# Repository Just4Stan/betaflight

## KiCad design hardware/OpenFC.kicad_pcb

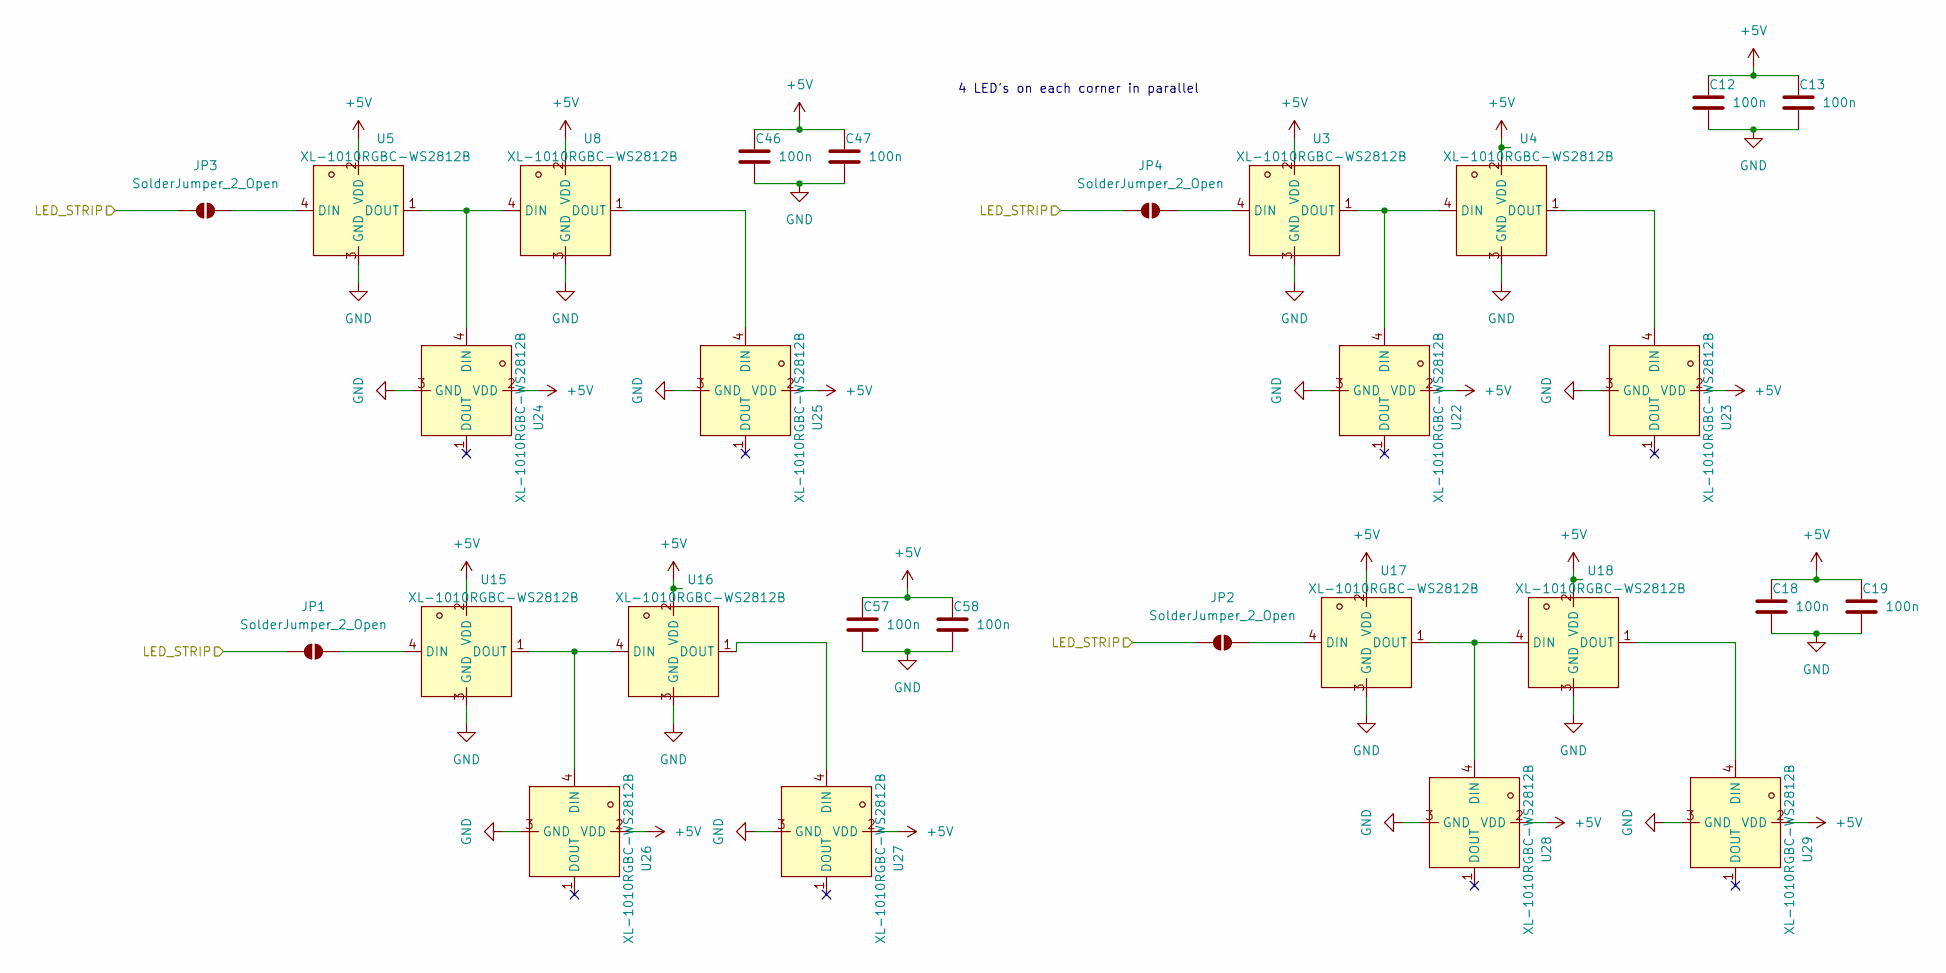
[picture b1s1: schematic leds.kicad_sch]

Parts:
C12, C13, C18, C19, C46, C47, C57, C58: 100n; C_0402_1005Metric; LCSC C1525
JP1, JP2, JP3, JP4: SolderJumper_2_Open; MouseBite-Slot-Jumper_0201
U3, U4, U5, U8, U15, U16, U17, U18, U22, U23, U24, U25, U26, U27, U28, U29: XL-1010RGBC-WS2812B; LED-SMD_4P-L1.0-W1.0-TL_XL-1010RGBC-WS2812B; LCSC Part C5349953

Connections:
+5V: C12.1, C13.1, C18.1, C19.1, C46.1, C47.1, C57.1, C58.1, U3.2 (VDD), U4.2 (VDD), U5.2 (VDD), U8.2 (VDD), U15.2 (VDD), U16.2 (VDD), U17.2 (VDD), U18.2 (VDD), U22.2 (VDD), U23.2 (VDD), U24.2 (VDD), U25.2 (VDD), U26.2 (VDD), U27.2 (VDD), U28.2 (VDD), U29.2 (VDD); also elsewhere on the board
/LED: JP1.1 (A), JP2.1 (A), JP3.1 (A), JP4.1 (A); also elsewhere on the board
GND: C12.2, C13.2, C18.2, C19.2, C46.2, C47.2, C57.2, C58.2, U3.3 (GND), U4.3 (GND), U5.3 (GND), U8.3 (GND), U15.3 (GND), U16.3 (GND), U17.3 (GND), U18.3 (GND), U22.3 (GND), U23.3 (GND), U24.3 (GND), U25.3 (GND), U26.3 (GND), U27.3 (GND), U28.3 (GND), U29.3 (GND); also elsewhere on the board
unnamed: JP1.2 (B), U15.4 (DIN)
unnamed: JP2.2 (B), U17.4 (DIN)
unnamed: JP3.2 (B), U5.4 (DIN)
unnamed: JP4.2 (B), U3.4 (DIN)
unnamed: U15.1 (DOUT), U16.4 (DIN), U26.4 (DIN)
unnamed: U16.1 (DOUT), U27.4 (DIN)
unnamed: U17.1 (DOUT), U18.4 (DIN), U28.4 (DIN)
unnamed: U18.1 (DOUT), U29.4 (DIN)
unnamed: U3.1 (DOUT), U4.4 (DIN), U22.4 (DIN)
unnamed: U4.1 (DOUT), U23.4 (DIN)
unnamed: U5.1 (DOUT), U8.4 (DIN), U24.4 (DIN)
unnamed: U8.1 (DOUT), U25.4 (DIN)

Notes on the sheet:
4 LED's on each corner in parallel

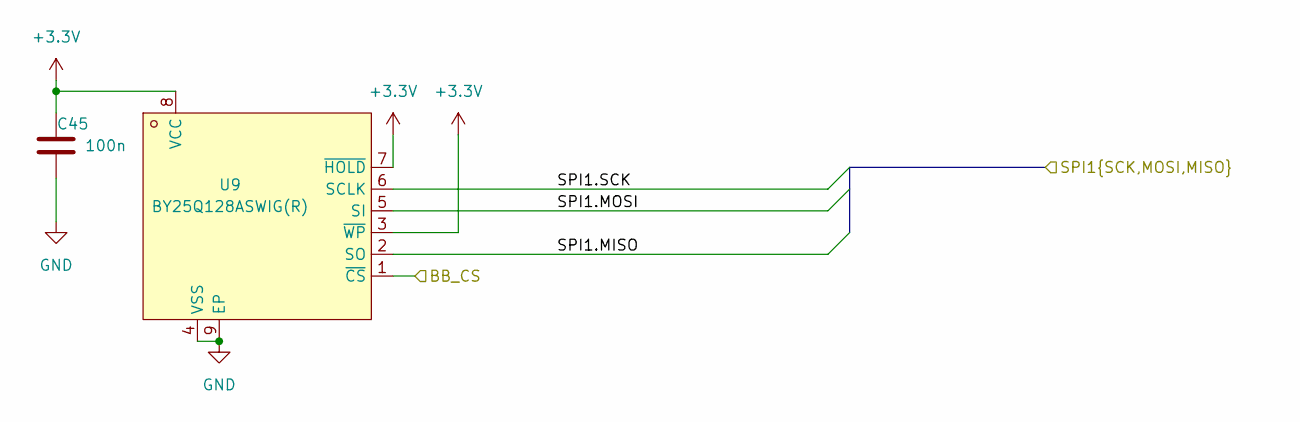
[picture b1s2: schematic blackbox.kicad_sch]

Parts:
C45: 100n; C_0402_1005Metric; LCSC C1525
U9: BY25Q128ASWIG(R); WSON-8_L6.0-W5.0-P1.27-BL-EP; LCSC Part C394872

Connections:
+3.3V: C45.1, U9.3 (~WP), U9.7 (~HOLD), U9.8 (VCC); also elsewhere on the board
/BLACKBOX/BB_CS: U9.1 (~CS); also elsewhere on the board
/BLACKBOX/SPI1.MISO: U9.2 (SO); also elsewhere on the board
/BLACKBOX/SPI1.MOSI: U9.5 (SI); also elsewhere on the board
/BLACKBOX/SPI1.SCK: U9.6 (SCLK); also elsewhere on the board
GND: C45.2, U9.4 (VSS), U9.9 (EP); also elsewhere on the board

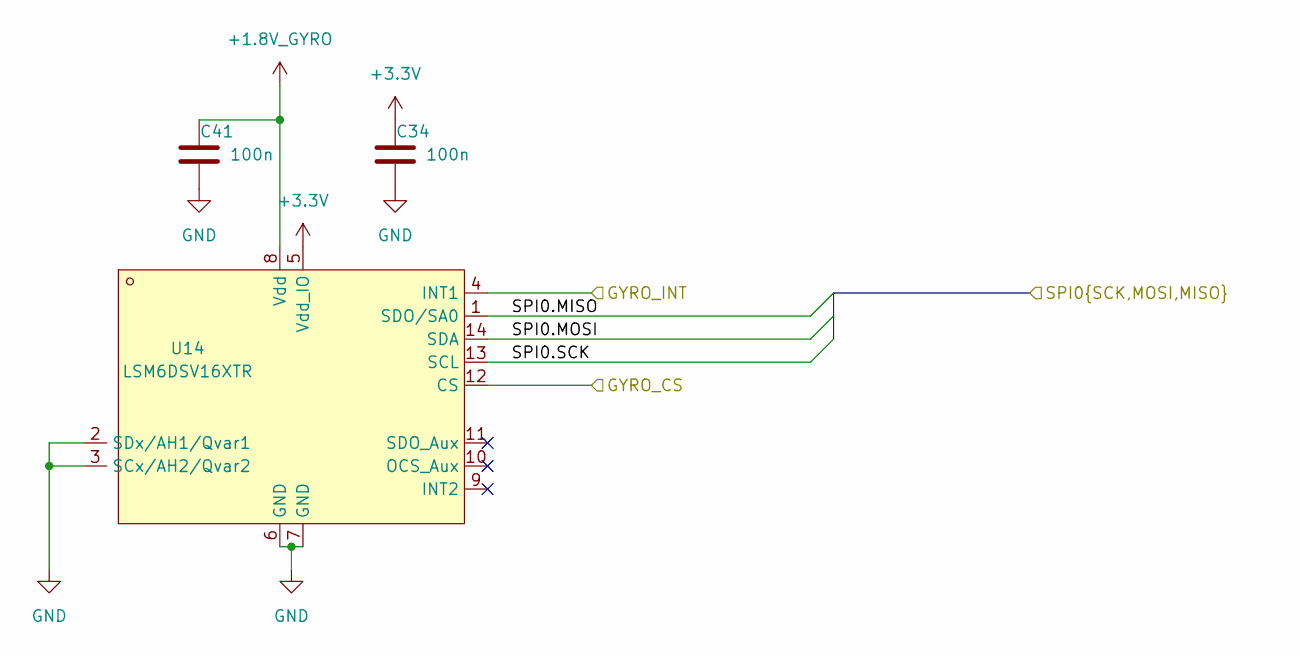
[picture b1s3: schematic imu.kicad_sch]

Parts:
C34, C41: 100n; C_0402_1005Metric; LCSC C1525
U14: LSM6DSV16XTR; LGA-14_L3.0-W2.5-P0.50-BR; LCSC Part C5267406

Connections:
+1.8V_GYRO: C41.1, U14.8 (Vdd); also elsewhere on the board
+3.3V: C34.1, U14.5 (Vdd_IO); also elsewhere on the board
/IMU/GYRO_CS: U14.12 (CS); also elsewhere on the board
/IMU/GYRO_INT: U14.4 (INT1); also elsewhere on the board
/IMU/SPI0.MISO: U14.1 (SDO/SA0); also elsewhere on the board
/IMU/SPI0.MOSI: U14.14 (SDA); also elsewhere on the board
/IMU/SPI0.SCK: U14.13 (SCL); also elsewhere on the board
GND: C34.2, C41.2, U14.2 (SDx/AH1/Qvar1), U14.3 (SCx/AH2/Qvar2), U14.6 (GND), U14.7 (GND); also elsewhere on the board

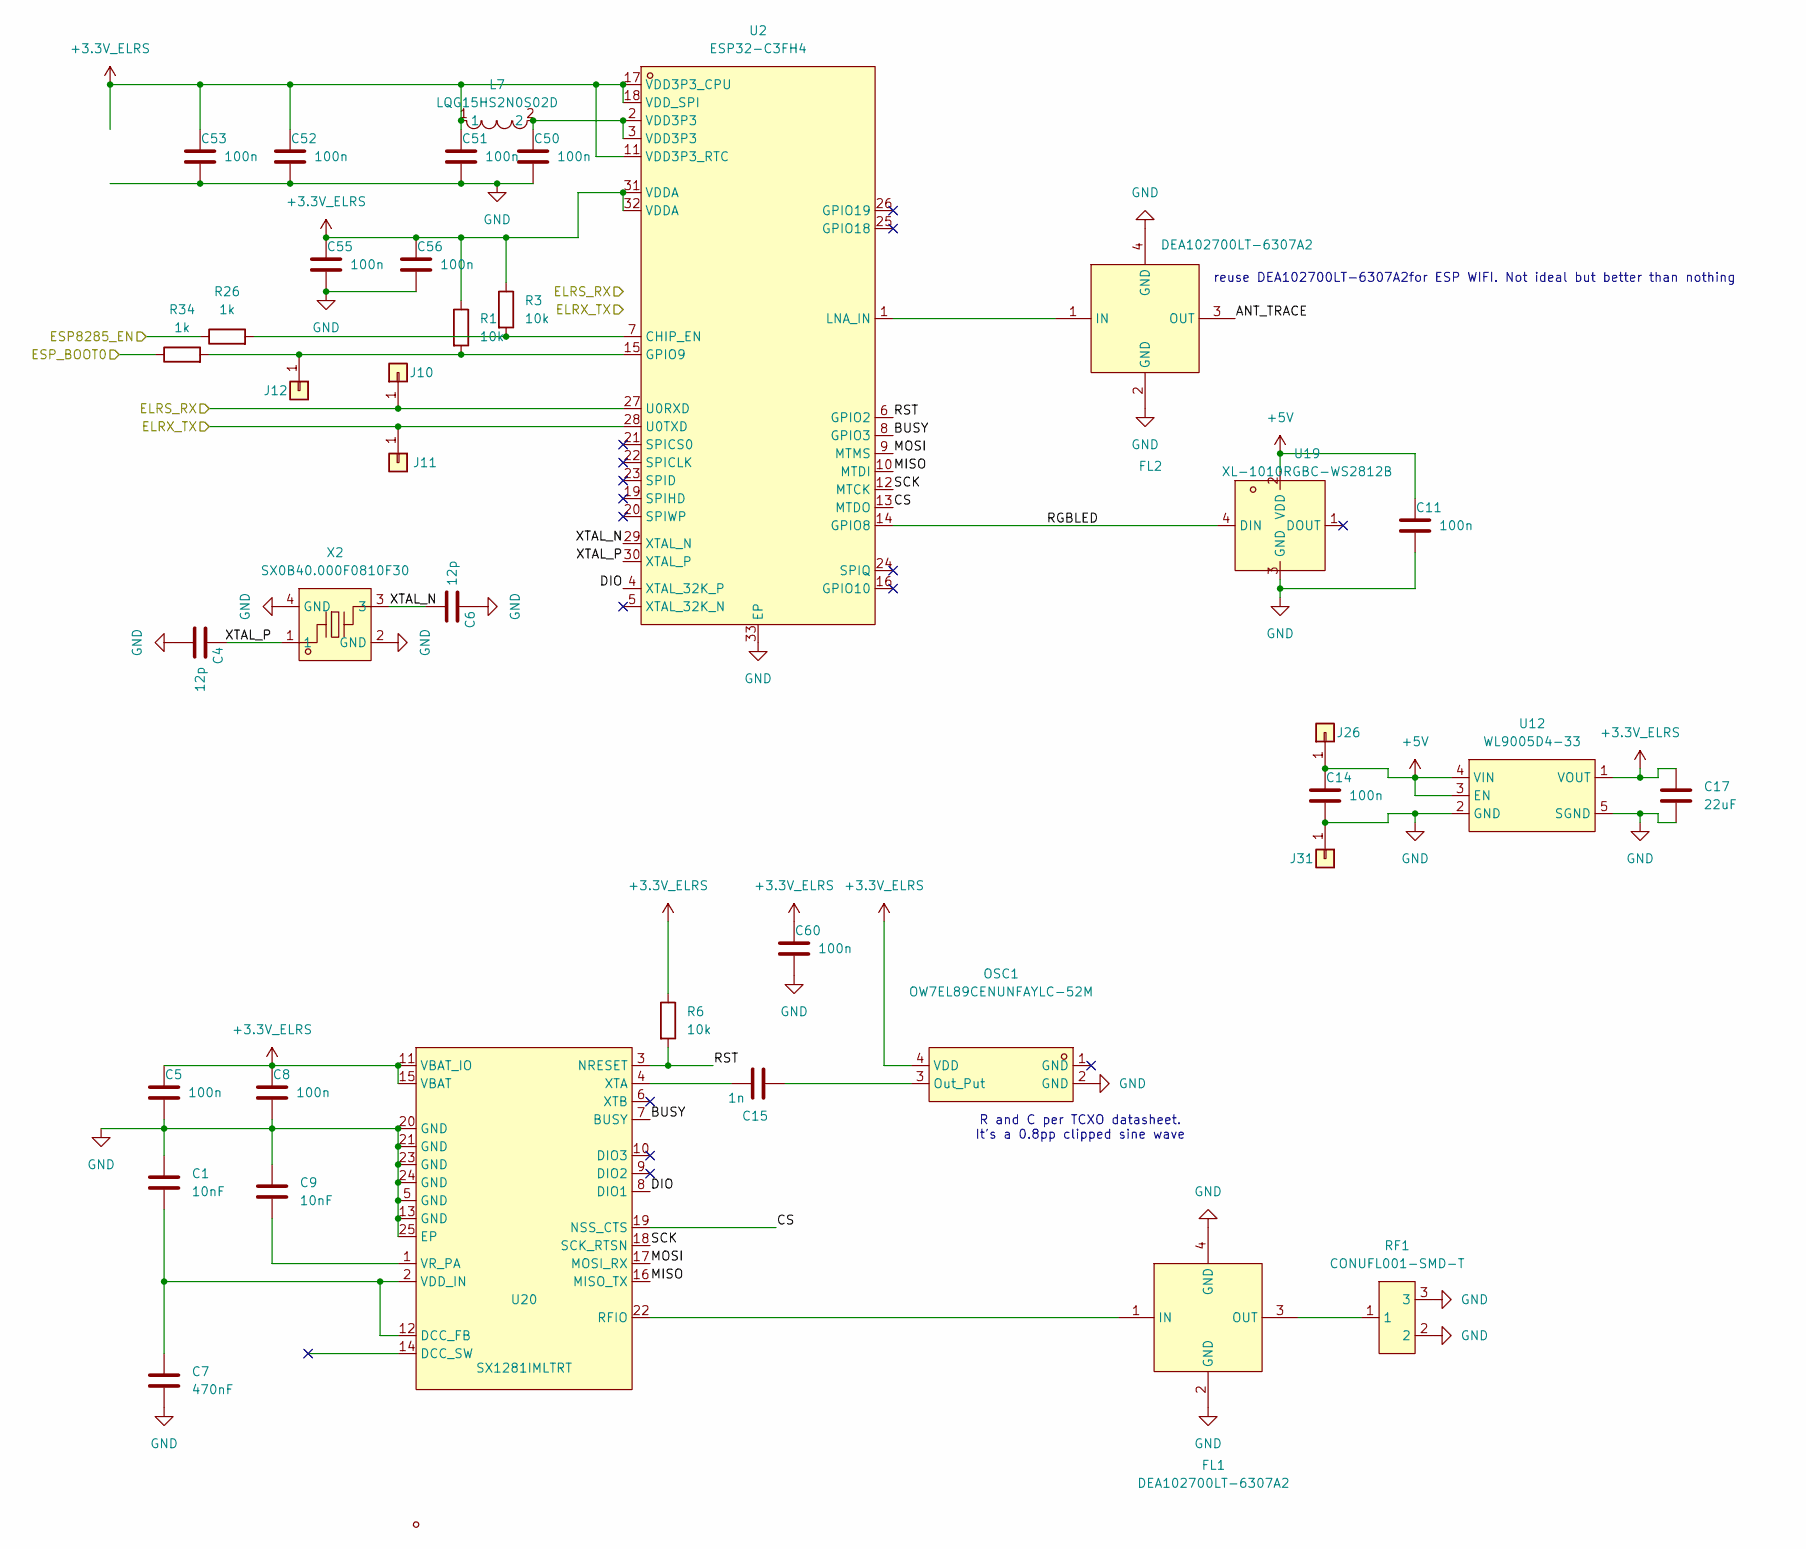
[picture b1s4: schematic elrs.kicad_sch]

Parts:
C1, C9: 10nF; C_0402_1005Metric; LCSC C15195
C4, C6: 12p; C_0402_1005Metric; LCSC C441742
C5, C8, C11, C14, C50, C51, C52, C53, C55, C56, C60: 100n; C_0402_1005Metric; LCSC C1525
C7: 470nF; C_0402_1005Metric; LCSC C92361
C15: 1n; C_0402_1005Metric
C17: 22uF; C_0402_1005Metric; LCSC C105226
FL1, FL2: DEA102700LT-6307A2; FILTER-SMD_4P-L1.0-W0.5-L; LCSC Part C574024
J10, J11, J12, J26, J31: 5V; small_pad
L7: LQG15HS2N0S02D; L0402; LCSC Part C18216
OSC1: OW7EL89CENUNFAYLC-52M; OSC-SMD_4P-L2.0-W1.6-BL_TXC_7Z; LCSC Part C22434896
R1, R3, R6: 10k; R_0402_1005Metric; LCSC C2909316
R26, R34: 1k; R_0402_1005Metric; LCSC C2909316
RF1: CONUFL001-SMD-T; IPEX-SMD_3P-L2.6-W2.6-LS3.0; LCSC Part C22418213
U2: ESP32-C3FH4; QFN-32_L5.0-W5.0-P0.50-TL-EP3.7; LCSC Part C2858491
U12: WL9005D4-33; UDFN-4_L1.0-W1.0-P0.65-TL; LCSC Part C5357206
U19: XL-1010RGBC-WS2812B; LED-SMD_4P-L1.0-W1.0-TL_XL-1010RGBC-WS2812B; LCSC Part C5349953
U20: SX1281IMLTRT; QFN-24_L4.0-W4.0-P0.50-TL-EP2.6; LCSC Part C2151551
X2: SX0B40.000F0810F30; CRYSTAL-SMD_4P-L1.6-W1.2-BL; LCSC Part C7301926

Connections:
+3.3V_ELRS: C5.1, C8.1, C17.1, C51.1, C52.1, C53.1, C55.1, C56.1, C60.1, L7.1, OSC1.4 (VDD), R1.1, R3.1, R6.1, U2.11 (VDD3P3_RTC), U2.17 (VDD3P3_CPU), U2.18 (VDD_SPI), U2.31 (VDDA), U2.32 (VDDA), U12.1 (VOUT), U20.11 (VBAT_IO), U20.15 (VBAT)
+5V: C11.1, C14.1, J26.1, U12.3 (EN), U12.4 (VIN), U19.2 (VDD); also elsewhere on the board
/ELRS/ANT_TRACE: FL2.3 (OUT)
/ELRS/BUSY: U2.8 (GPIO3), U20.7 (BUSY)
/ELRS/CS: U2.13 (MTDO), U20.19 (NSS_CTS)
/ELRS/DIO: U2.4 (XTAL_32K_P), U20.8 (DIO1)
/ELRS/ESP8285_EN: R26.1; also elsewhere on the board
/ELRS/ESP_BOOT0: R34.1; also elsewhere on the board
/ELRS/MISO: U2.10 (MTDI), U20.16 (MISO_TX)
/ELRS/MOSI: U2.9 (MTMS), U20.17 (MOSI_RX)
/ELRS/RGBLED: U2.14 (GPIO8), U19.4 (DIN)
/ELRS/RST: R6.2, U2.6 (GPIO2), U20.3 (NRESET)
/ELRS/SCK: U2.12 (MTCK), U20.18 (SCK_RTSN)
/ELRS/XTAL_N: C6.2, U2.29 (XTAL_N), X2.3
/ELRS/XTAL_P: C4.1, U2.30 (XTAL_P), X2.1
/UART1_RX: J11.1, U2.28 (U0TXD); also elsewhere on the board
/UART1_TX: J10.1, U2.27 (U0RXD); also elsewhere on the board
GND: C1.1, C4.2, C5.2, C6.1, C7.2, C8.2, C9.1, C11.2, C14.2, C17.2, C50.2, C51.2, C52.2, C53.2, C55.2, C56.2, C60.2, FL1.2 (GND), FL1.4 (GND), FL2.2 (GND), FL2.4 (GND), J31.1, OSC1.2 (GND), RF1.2, RF1.3, U2.33 (EP), U12.2 (GND), U12.5 (SGND), U19.3 (GND), U20.5 (GND), U20.13 (GND), U20.20 (GND), U20.21 (GND), U20.23 (GND), U20.24 (GND), U20.25 (EP), X2.2 (GND), X2.4 (GND); also elsewhere on the board
unnamed: C50.1, L7.2, U2.2 (VDD3P3), U2.3 (VDD3P3)
unnamed: FL1.1 (IN), U20.22 (RFIO)
unnamed: FL1.3 (OUT), RF1.1
unnamed: FL2.1 (IN), U2.1 (LNA_IN)
unnamed: J12.1, R1.2, R34.2, U2.15 (GPIO9)
unnamed: C15.2, OSC1.3 (Out_Put)
unnamed: R3.2, R26.2, U2.7 (CHIP_EN)
unnamed: C1.2, C7.1, U20.2 (VDD_IN), U20.12 (DCC_FB)
unnamed: C9.2, U20.1 (VR_PA)
unnamed: C15.1, U20.4 (XTA)

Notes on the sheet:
reuse DEA102700LT-6307A2for ESP WIFI. Not ideal but better than nothing
R and C per TCXO datasheet. It's a 0.8pp clipped sine wave

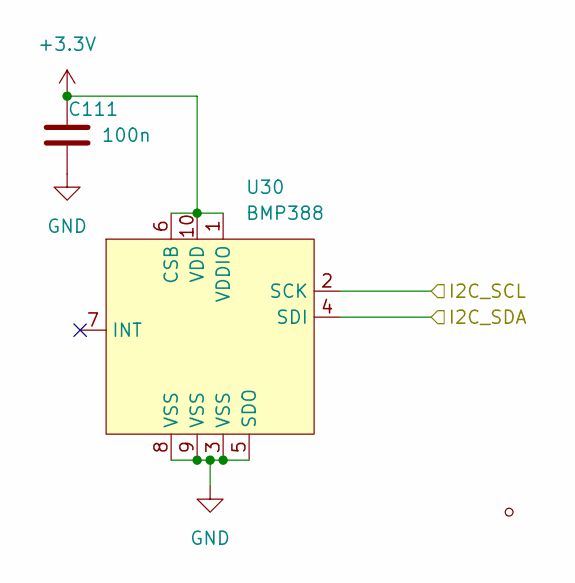
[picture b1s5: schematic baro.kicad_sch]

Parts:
C111: 100n; C_0402_1005Metric; LCSC C1525
U30: BMP388; SENSORM-SMD_BMP388; LCSC Part C779278

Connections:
+3.3V: C111.1, U30.1 (VDDIO), U30.6 (CSB), U30.10 (VDD); also elsewhere on the board
/I2C_SCL: U30.2 (SCK); also elsewhere on the board
/I2C_SDA: U30.4 (SDI); also elsewhere on the board
GND: C111.2, U30.3 (VSS), U30.5 (SDO), U30.8 (VSS), U30.9 (VSS); also elsewhere on the board

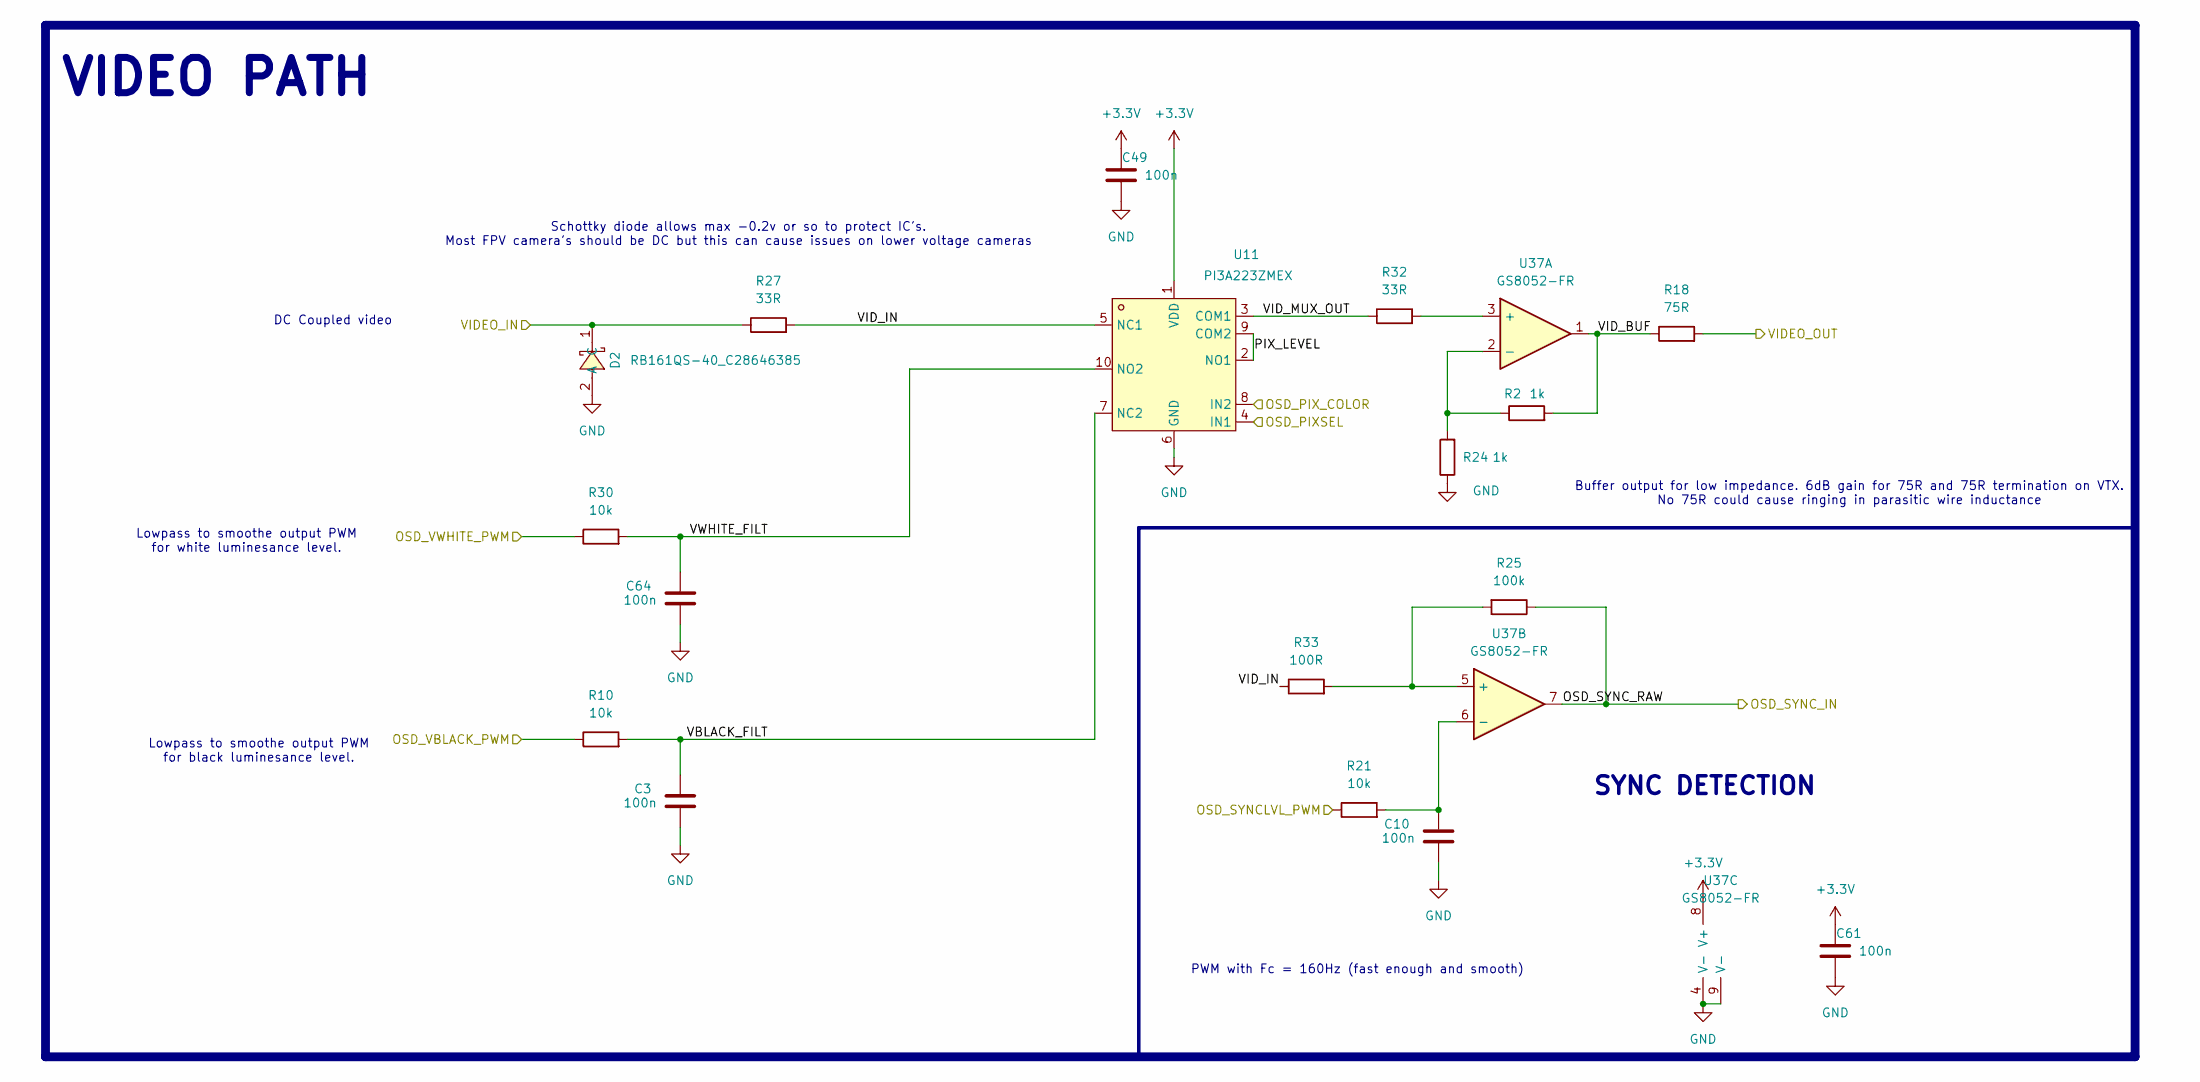
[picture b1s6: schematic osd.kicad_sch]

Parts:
C3, C10, C49, C61, C64: 100n; C_0402_1005Metric; LCSC C1525
D2: RB161QS-40_C28646385; SOD-882_L1.0-W0.6-RD; LCSC Part C28646385
R2, R24: 1k; R_0402_1005Metric
R10, R21, R30: 10k; R_0402_1005Metric
R18: 75R; R_0402_1005Metric
R25: 100k; R_0402_1005Metric
R27, R32: 33R; R_0402_1005Metric
R33: 100R; R_0402_1005Metric
U11: PI3A223ZMEX; UQFN-10_L1.8-W1.4-P0.40-TL; LCSC Part C2673436
U37: GS8052-FR; WSON-8-1EP_2x2mm_P0.5mm_EP0.9x1.6mm; LCSC C605423

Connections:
+3.3V: C49.1, C61.1, U11.1 (VDD), U37.8 (V+); also elsewhere on the board
/OSD/OSD_PIXSEL: U11.4 (IN1); also elsewhere on the board
/OSD/OSD_PIX_COLOR: U11.8 (IN2); also elsewhere on the board
/OSD/OSD_SYNCLVL_PWM: R21.1; also elsewhere on the board
/OSD/OSD_SYNC_RAW: R25.1, U37.7; also elsewhere on the board
/OSD/OSD_VBLACK_PWM: R10.1; also elsewhere on the board
/OSD/OSD_VWHITE_PWM: R30.1; also elsewhere on the board
/OSD/PIX_LEVEL: U11.2 (NO1), U11.9 (COM2)
/OSD/VBLACK_FILT: C3.2, R10.2, U11.7 (NC2); also elsewhere on the board
/OSD/VIDEO_IN: D2.1 (C), R27.1; also elsewhere on the board
/OSD/VIDEO_OUT: R18.2; also elsewhere on the board
/OSD/VID_BUF: R2.2, R18.1, U37.1
/OSD/VID_IN: R27.2, R33.1, U11.5 (NC1); also elsewhere on the board
/OSD/VID_MUX_OUT: R32.1, U11.3 (COM1); also elsewhere on the board
/OSD/VWHITE_FILT: C64.2, R30.2, U11.10 (NO2); also elsewhere on the board
GND: C3.1, C10.1, C49.2, C61.2, C64.1, D2.2 (A), R24.1, U11.6 (GND), U37.4 (V-), U37.9 (V-); also elsewhere on the board
unnamed: R32.2, U37.3 (+)
unnamed: R2.1, R24.2, U37.2 (-)
unnamed: R25.2, R33.2, U37.5 (+)
unnamed 131: C10.2, R21.2, U37.6 (-); also elsewhere on the board

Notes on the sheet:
PWM with Fc = 160Hz (fast enough and smooth)
DC Coupled video
Buffer output for low impedance. 6dB gain for 75R and 75R termination on VTX. No 75R could cause ringing in parasitic wire inductance
VIDEO PATH
SYNC DETECTION
Lowpass to smoothe output PWM for white luminesance level.
Lowpass to smoothe output PWM for black luminesance level.
Schottky diode allows max -0.2v or so to protect IC's. Most FPV camera's should be DC but this can cause issues on lower voltage cameras

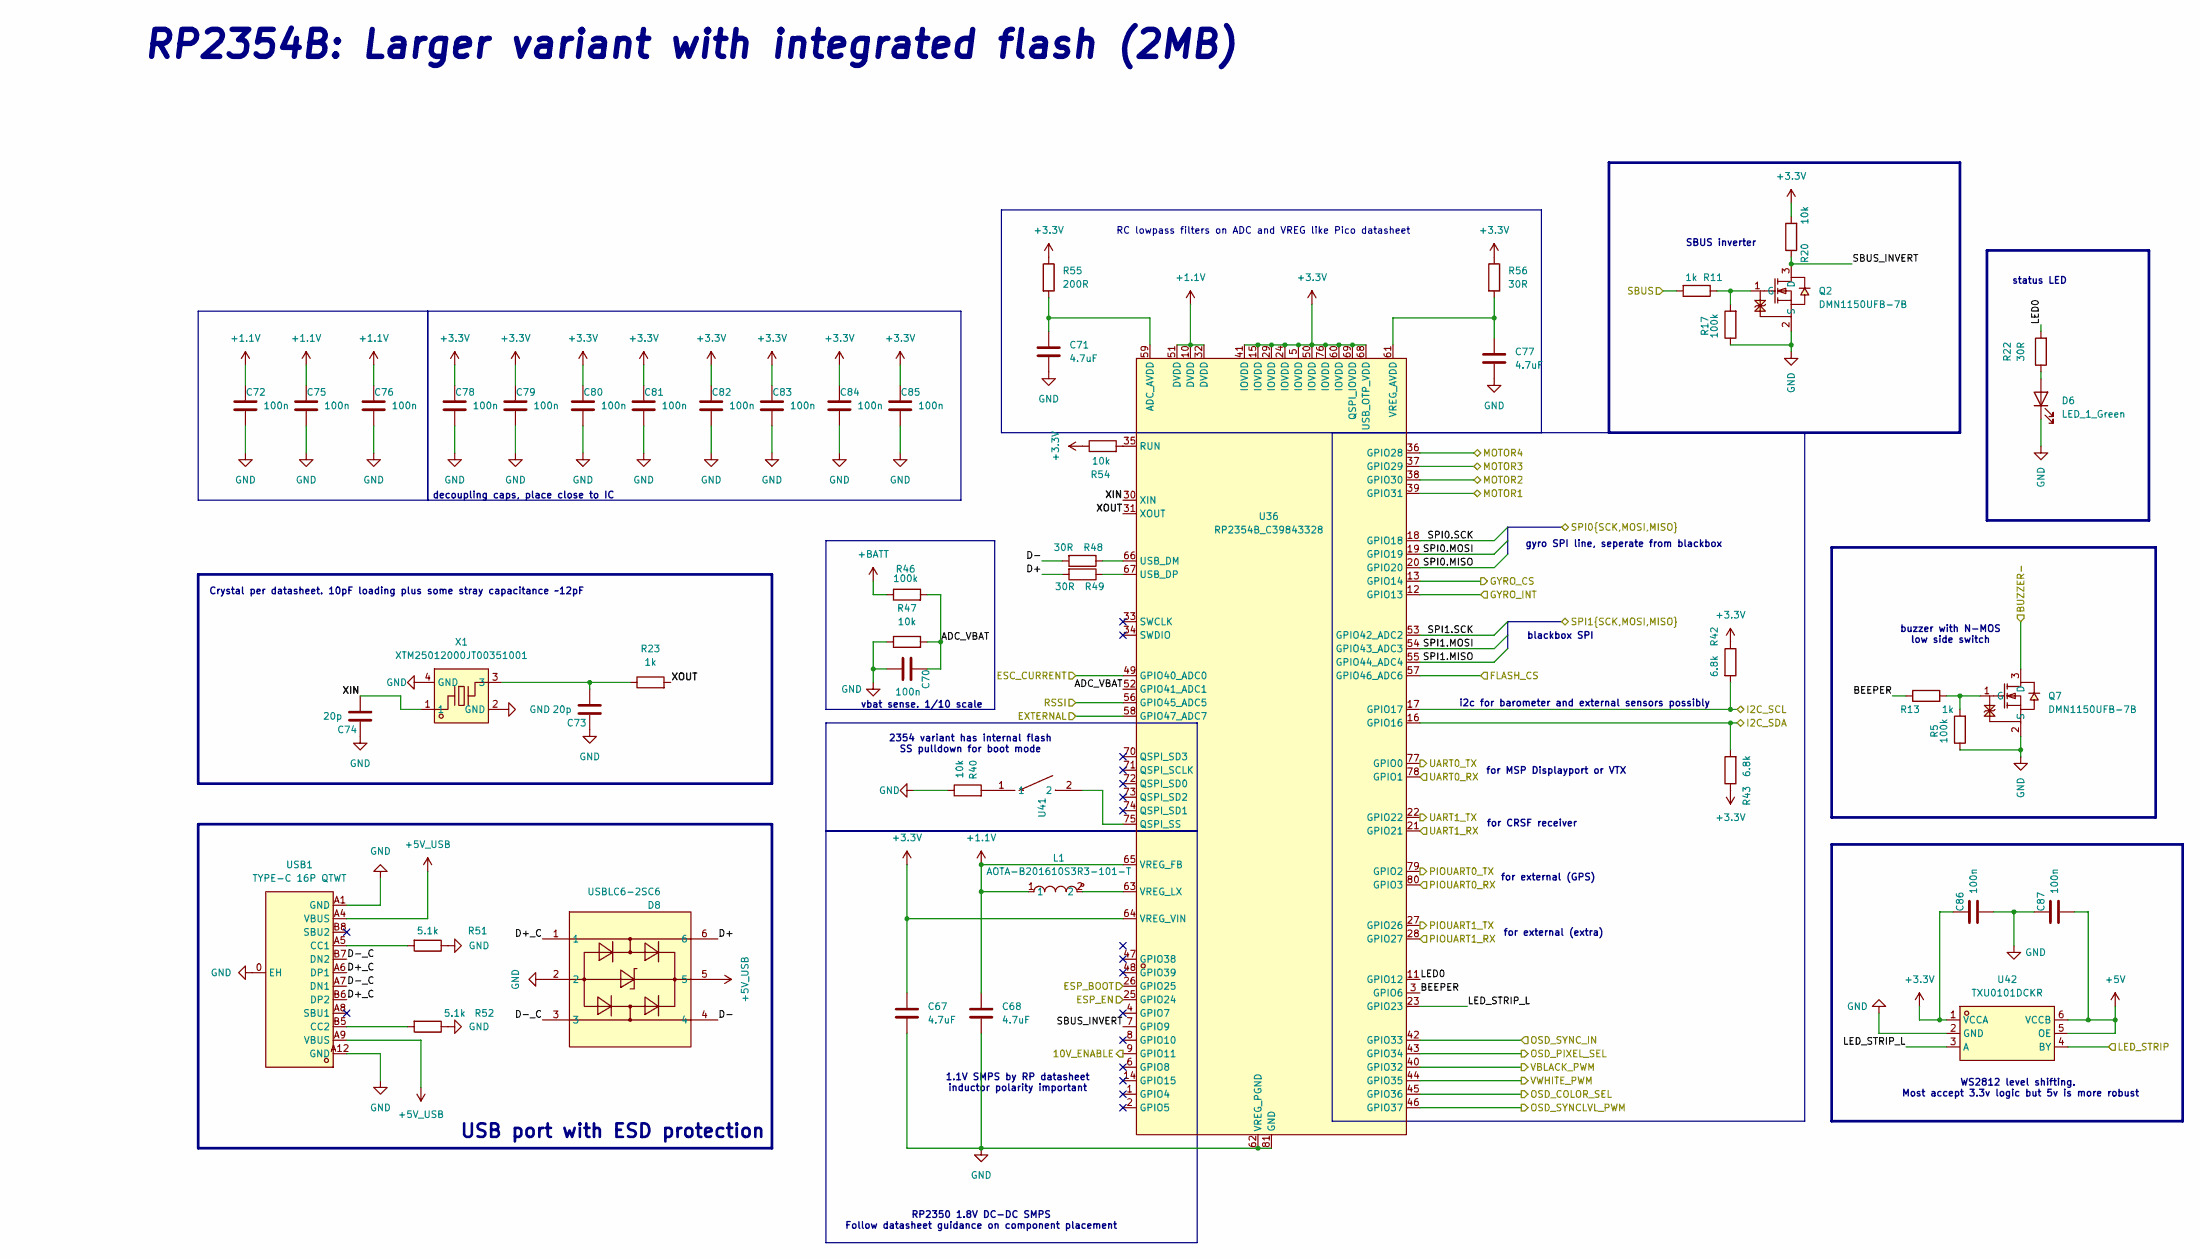
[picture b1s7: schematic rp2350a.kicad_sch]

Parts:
C67, C68, C71, C77: 4.7uF; C_0402_1005Metric; LCSC C23733
C70, C72, C75, C76, C78, C79, C80, C81, C82, C83, C84, C85, C86, C87: 100n; C_0402_1005Metric; LCSC C1525
C73, C74: 20p; C_0402_1005Metric; LCSC C441742
D6: LED_1_Green; LED_0603_1608Metric; LCSC C2994781
D8: USBLC6-2SC6; SOT-23-6_L2.9-W1.6-P0.95-LS2.8-BL; LCSC Part C7519
L1: AOTA-B201610S3R3-101-T; IND-SMD_L2.0-W1.6_AOTA-B201610S3R3-101-T; LCSC Part C42411119
Q2, Q7: DMN1150UFB-7B; DFN-3L_L1.0-W0.6-P0.65-BR; LCSC Part C459538
R5, R17, R46: 100k; R_0402_1005Metric; LCSC C60491
R11, R13: 1k; R_0402_1005Metric; LCSC C106235
R20: 10k; R_0402_1005Metric; LCSC C106235
R22, R48, R49, R56: 30R; R_0402_1005Metric; LCSC C138007
R23: 1k; R_0402_1005Metric; LCSC C2909316
R40, R47, R54: 10k; R_0402_1005Metric; LCSC C2909316
R42: 6.8k; R_0402_1005Metric; LCSC C105872
R43: 6.8k; R_0402_1005Metric; LCSC C2906876
R51, R52: 5.1k; R_0402_1005Metric; LCSC C105872
R55: 200R; R_0402_1005Metric; LCSC C25087
U36: RP2354B_C39843328; QFN-80_L10.0-W10.0-P0.40-TL-EP3.4; LCSC Part C39843328
U41: TS2306A 240GF MSM 9_C2976675; SW-SMD_4P-L3.0-W2.0-P0.85-LS3.5; LCSC Part C2976675
U42: TXU0101DCKR; SC-70-6_L2.0-W1.3-P0.65-LS2.1-BL; LCSC Part C5217868
USB1: TYPE-C 16P QTWT; USB-TYPE-C-SMD_TYPE-C-16P-QTWT; LCSC Part C5187472
X1: XTM25012000JT00351001; CRYSTAL-SMD_4P-L2.5-W2.0-BL-A; LCSC Part C37635340

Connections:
+1.1V: C68.1, C72.1, C75.1, C76.1, L1.1, U36.10 (DVDD), U36.32 (DVDD), U36.51 (DVDD), U36.65 (VREG_FB)
+3.3V: C67.1, C78.1, C79.1, C80.1, C81.1, C82.1, C83.1, C84.1, C85.1, C86.1, R20.2, R42.1, R43.1, R54.1, R55.1, R56.1, U36.5 (IOVDD), U36.15 (IOVDD), U36.24 (IOVDD), U36.29 (IOVDD), U36.41 (IOVDD), U36.50 (IOVDD), U36.60 (IOVDD), U36.64 (VREG_VIN), U36.68 (USB_OTP_VDD), U36.69 (QSPI_IOVDD), U36.76 (IOVDD), U42.1 (VCCA); also elsewhere on the board
+5V: C87.2, U42.5 (OE), U42.6 (VCCB); also elsewhere on the board
+5V_USB: D8.5, USB1.A4 (VBUS), USB1.A9 (VBUS); also elsewhere on the board
+BATT: R46.1; also elsewhere on the board
/BLACKBOX/BB_CS: U36.57 (GPIO46_ADC6); also elsewhere on the board
/BLACKBOX/SPI1.MISO: U36.55 (GPIO44_ADC4); also elsewhere on the board
/BLACKBOX/SPI1.MOSI: U36.54 (GPIO43_ADC3); also elsewhere on the board
/BLACKBOX/SPI1.SCK: U36.53 (GPIO42_ADC2); also elsewhere on the board
/ELRS/ESP8285_EN: U36.25 (GPIO24); also elsewhere on the board
/ELRS/ESP_BOOT0: U36.26 (GPIO25); also elsewhere on the board
/I2C_SCL: R42.2, U36.17 (GPIO17); also elsewhere on the board
/I2C_SDA: R43.2, U36.16 (GPIO16); also elsewhere on the board
/IMU/GYRO_CS: U36.13 (GPIO14); also elsewhere on the board
/IMU/GYRO_INT: U36.12 (GPIO13); also elsewhere on the board
/IMU/SPI0.MISO: U36.20 (GPIO20); also elsewhere on the board
/IMU/SPI0.MOSI: U36.19 (GPIO19); also elsewhere on the board
/IMU/SPI0.SCK: U36.18 (GPIO18); also elsewhere on the board
/LED: U42.4 (BY); also elsewhere on the board
/OSD/OSD_PIXSEL: U36.43 (GPIO34); also elsewhere on the board
/OSD/OSD_PIX_COLOR: U36.45 (GPIO36); also elsewhere on the board
/OSD/OSD_SYNCLVL_PWM: U36.46 (GPIO37); also elsewhere on the board
/OSD/OSD_SYNC_RAW: U36.42 (GPIO33); also elsewhere on the board
/OSD/OSD_VBLACK_PWM: U36.40 (GPIO32); also elsewhere on the board
/OSD/OSD_VWHITE_PWM: U36.44 (GPIO35); also elsewhere on the board
/PADS/ADC2: U36.58 (GPIO47_ADC7); also elsewhere on the board
/PADS/BUZZER-: Q7.3 (D); also elsewhere on the board
/PADS/CURRENT: U36.49 (GPIO40_ADC0); also elsewhere on the board
/PADS/DIGITAL_RX: U36.78 (GPIO1); also elsewhere on the board
/PADS/DIGITAL_TX: U36.77 (GPIO0); also elsewhere on the board
/PADS/M1: U36.39 (GPIO31); also elsewhere on the board
/PADS/M2: U36.38 (GPIO30); also elsewhere on the board
/PADS/M3: U36.37 (GPIO29); also elsewhere on the board
/PADS/M4: U36.36 (GPIO28); also elsewhere on the board
/PADS/PIOUART0_RX: U36.80 (GPIO3); also elsewhere on the board
/PADS/PIOUART0_TX: U36.79 (GPIO2); also elsewhere on the board
/PADS/PIOUART1_RX: U36.28 (GPIO27); also elsewhere on the board
/PADS/PIOUART1_TX: U36.27 (GPIO26); also elsewhere on the board
/PADS/RSSI: U36.56 (GPIO45_ADC5); also elsewhere on the board
/PADS/SBUS: R11.2; also elsewhere on the board
/RP2350A/ADC_VBAT: C70.1, R46.2, R47.2, U36.52 (GPIO41_ADC1)
/RP2350A/BEEPER: R13.1, U36.3 (GPIO6)
/RP2350A/D+: D8.6, R49.2
/RP2350A/D+_C: D8.1, USB1.A6 (DP1), USB1.B6 (DP2)
/RP2350A/D-: D8.4, R48.2
/RP2350A/D-_C: D8.3, USB1.A7 (DN1), USB1.B7 (DN2)
/RP2350A/LED0: R22.2, U36.11 (GPIO12)
/RP2350A/LED_STRIP_L: U36.23 (GPIO23), U42.3 (A); also elsewhere on the board
/RP2350A/SBUS_INVERT: Q2.3 (D), R20.1, U36.7 (GPIO9); also elsewhere on the board
/RP2350A/XIN: C74.2, U36.30 (XIN), X1.1
/RP2350A/XOUT: R23.2, U36.31 (XOUT)
/UART1_RX: U36.21 (GPIO21); also elsewhere on the board
/UART1_TX: U36.22 (GPIO22); also elsewhere on the board
GND: C67.2, C68.2, C70.2, C71.2, C72.2, C73.1, C74.1, C75.2, C76.2, C77.2, C78.2, C79.2, C80.2, C81.2, C82.2, C83.2, C84.2, C85.2, C86.2, C87.1, D6.1 (K), D8.2, Q2.2 (S), Q7.2 (S), R5.1, R17.1, R40.1, R47.1, R51.1, R52.1, U36.62 (VREG_PGND), U36.81 (GND), U42.2 (GND), USB1.0 (EH), USB1.A1 (GND), USB1.A12 (GND), X1.2 (GND), X1.4 (GND); also elsewhere on the board
unnamed: C73.2, R23.1, X1.3
unnamed: D6.2 (A), R22.1
unnamed: Q2.1 (G), R11.1, R17.2
unnamed: Q7.1 (G), R5.2, R13.2
unnamed: R40.2, U41.1
unnamed: C71.1, R55.2, U36.59 (ADC_AVDD)
unnamed: U36.75 (QSPI_SS), U41.2
unnamed: R54.2, U36.35 (RUN)
unnamed 122: U36.33 (SWCLK); also elsewhere on the board
unnamed 123: U36.34 (SWDIO); also elsewhere on the board
unnamed: R48.1, U36.66 (USB_DM)
unnamed: R49.1, U36.67 (USB_DP)
unnamed: C77.1, R56.2, U36.61 (VREG_AVDD)
unnamed: L1.2, U36.63 (VREG_LX)
unnamed: R51.2, USB1.A5 (CC1)
unnamed: R52.2, USB1.B5 (CC2)

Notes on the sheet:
vbat sense. 1/10 scale
RP2354B: Larger variant with integrated flash (2MB)
blackbox SPI
buzzer with N-MOS low side switch
for MSP Displayport or VTX
2354 variant has internal flash SS pulldown for boot mode
RP2350 1.8V DC-DC SMPS Follow datasheet guidance on component placement
for CRSF receiver
gyro SPI line, seperate from blackbox
decoupling caps, place close to IC
for external (extra)
status LED
Crystal per datasheet. 10pF loading plus some stray capacitance ~12pF
for external (GPS)
i2c for barometer and external sensors possibly
SBUS inverter
RC lowpass filters on ADC and VREG like Pico datasheet
WS2812 level shifting. Most accept 3.3v logic but 5v is more robust
USB port with ESD protection
1.1V SMPS by RP datasheet inductor polarity important

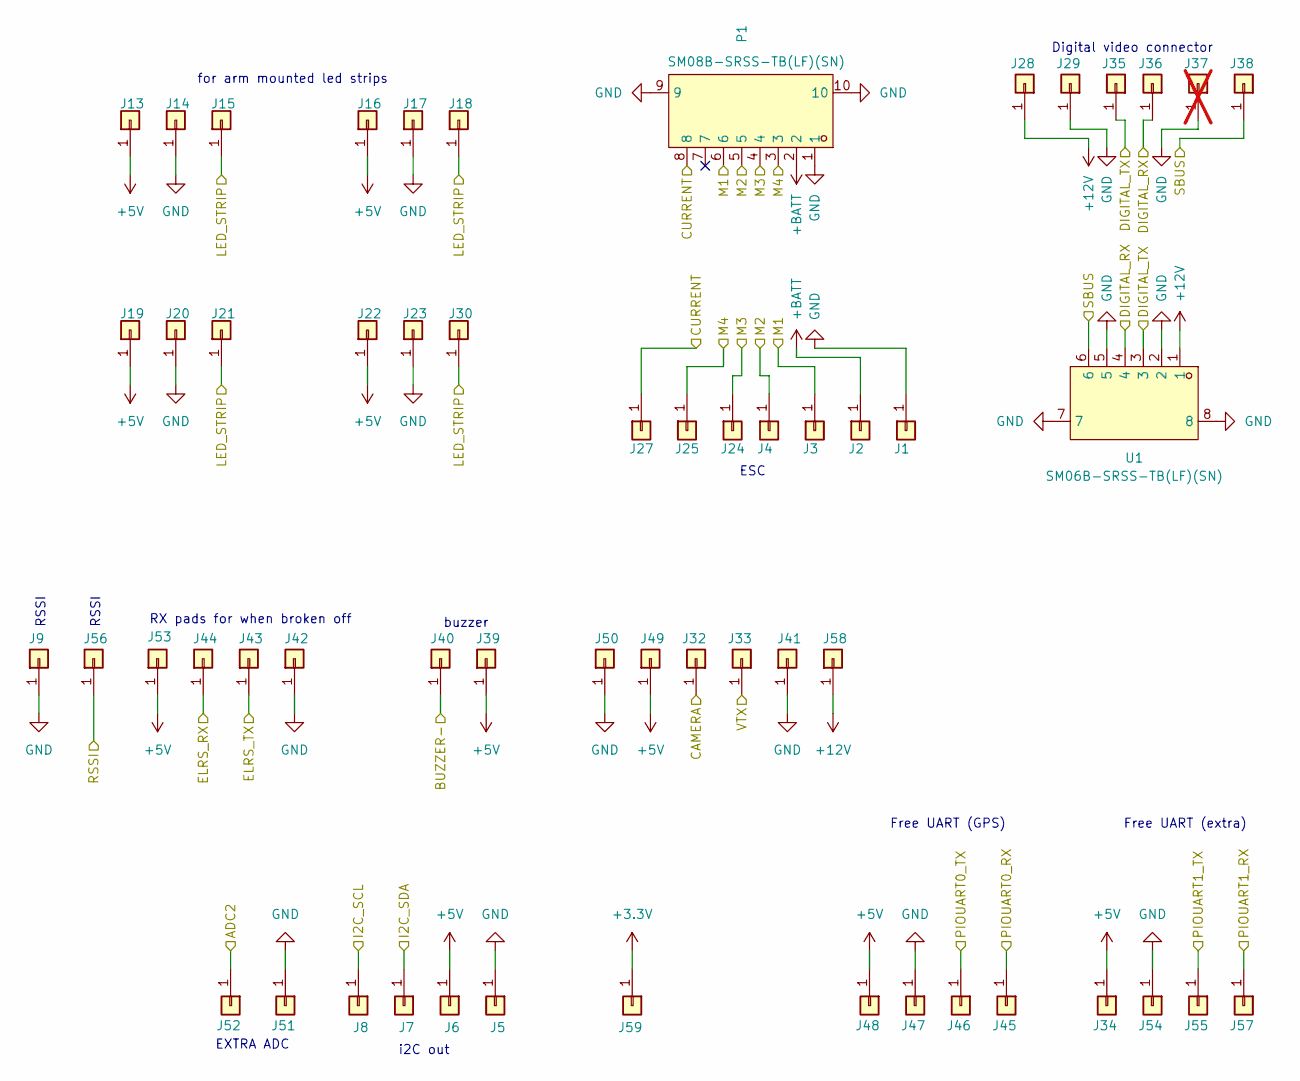
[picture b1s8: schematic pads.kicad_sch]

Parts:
J1, J2, J3, J4, J5, J6, J7, J8, J9, J13, J14, J15, J16, J17, J18, J19, J20, J21, J22, J23, J24, J25, J27, J28, J29, J30, J32, J33, J34, J35, J36, J38, J39, J40, J41, J42, J43, J44, J45, J46, J47, J48, J49, J50, J51, J52, J53, J54, J55, J56, J57, J58, J59: 5V; small_pad
J37: 5V; small_pad; not fitted
P1: SM08B-SRSS-TB(LF)(SN); CONN-TH_SM08B-SRSS-TB-LF-SN; LCSC Part C160407
U1: SM06B-SRSS-TB(LF)(SN); CONN-SMD_SM06B-SRSS-TB-LF-SN; LCSC Part C160405

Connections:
+3.3V: J59.1; also elsewhere on the board
+5V: J6.1, J13.1, J16.1, J19.1, J22.1, J34.1, J39.1, J48.1, J49.1, J53.1; also elsewhere on the board
+12V: J28.1, J58.1, U1.1; also elsewhere on the board
+BATT: J2.1, P1.2; also elsewhere on the board
/I2C_SCL: J8.1; also elsewhere on the board
/I2C_SDA: J7.1; also elsewhere on the board
/LED: J15.1, J18.1, J21.1, J30.1; also elsewhere on the board
/OSD/VIDEO_IN: J32.1; also elsewhere on the board
/OSD/VIDEO_OUT: J33.1; also elsewhere on the board
/PADS/ADC2: J52.1; also elsewhere on the board
/PADS/BUZZER-: J40.1; also elsewhere on the board
/PADS/CURRENT: J27.1, P1.8; also elsewhere on the board
/PADS/DIGITAL_RX: J36.1, U1.4; also elsewhere on the board
/PADS/DIGITAL_TX: J35.1, U1.3; also elsewhere on the board
/PADS/M1: J3.1, P1.6; also elsewhere on the board
/PADS/M2: J4.1, P1.5; also elsewhere on the board
/PADS/M3: J24.1, P1.4; also elsewhere on the board
/PADS/M4: J25.1, P1.3; also elsewhere on the board
/PADS/PIOUART0_RX: J45.1; also elsewhere on the board
/PADS/PIOUART0_TX: J46.1; also elsewhere on the board
/PADS/PIOUART1_RX: J57.1; also elsewhere on the board
/PADS/PIOUART1_TX: J55.1; also elsewhere on the board
/PADS/RSSI: J56.1; also elsewhere on the board
/PADS/SBUS: J38.1, U1.6; also elsewhere on the board
/UART1_RX: J44.1; also elsewhere on the board
/UART1_TX: J43.1; also elsewhere on the board
GND: J1.1, J5.1, J9.1, J14.1, J17.1, J20.1, J23.1, J29.1, J37.1, J41.1, J42.1, J47.1, J50.1, J51.1, J54.1, P1.1, P1.9, P1.10, U1.2, U1.5, U1.7, U1.8; also elsewhere on the board

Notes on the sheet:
RSSI
Free UART (GPS)
i2C out
Free UART (extra)
buzzer
RX pads for when broken off
ESC
Digital video connector
EXTRA ADC
for arm mounted led strips
